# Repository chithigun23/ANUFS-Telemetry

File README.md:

# ANUFS Telemetry

Data-logging and telemetry module for the ANUFS vehicle: an STM32H523 board that listens on two CAN buses, fuses dual-antenna GNSS and an IMU with them, and logs everything to two microSD cards.

| Folder | What is in it | Start here |
|---|---|---|
| [hardware/](hardware/) | KiCad project, fabrication files, BOM, power budget, RF analysis | [hardware/README.md](hardware/README.md) |
| [software/](software/) | Rust firmware crates, host tools and diagrams | [software/README.md](software/README.md) |

## Where things stand

- **Hardware:** boards are ordered and will be assembled by hand. Fit R10 as 73.2k (the BOM is up to date). Fit J12 as the SWD header until the Tag-Connect cable arrives.
- **Software:** every logic crate and host tool is written and tested on the PC (332 tests), and the firmware (a bring-up self-test and the logger) builds for the chip. Nothing has run on the board yet; assembly is in [hardware/ASSEMBLY.md](hardware/ASSEMBLY.md) and the bring-up order is in [software/README.md](software/README.md).
- **Waiting on you:** the MoTeC CAN configuration (bit rate and message layouts), and a debug probe.

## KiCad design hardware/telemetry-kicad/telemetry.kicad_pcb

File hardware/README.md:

# ANUFS Telemetry

STM32H5-based data-logging and telemetry module for the ANUFS vehicle. It sits on two of the car's CAN buses, fuses IMU + dual-antenna GNSS data with bus traffic, logs everything to two microSD cards, drives onboard status LEDs, and exposes USB-C for bench debug.

Reference designators below come from the current netlist (`telemetry.net`, exported 2026-10-13).

## Architecture

- **Power** - the board runs from the vehicle's 12V harness input (`J1`), through `D2` (SMBJ16A TVS) and `F1` (1.5A polyfuse), then `Q1` (P-FET reverse-polarity protection, gate clamped by `D1`) into `U2` (TPS2121), which arbitrates between that battery feed and USB-C bus power (via `D3`) so the board can run on the bench without the car. The over-voltage lockout on the battery input is set by the `U2` OV1 divider (`R10` 73.2k / `R12` 5k). The muxed rail (`V_IN`) feeds two independent regulators: `U1` (LMR33610) bucks it to the **+3.3V rail that powers everything else on the board**, while `U5` (LM2940-5.0) makes a separate **+5V rail that goes only to the status LEDs' common anodes**.
- **Compute** - `U6`, an STM32H523RCT7 (Cortex-M33), is the hub. It is clocked from a 24MHz crystal (`Y1`). `SW3` is the NRST button and `SW4` pulls BOOT0 high (with `R34` pull-down) for the system bootloader.
- **Sensing** - `U3` (ASM330LHHX) is a 6-axis IMU wired to the MCU over SPI (CS, SCK, SDI, SDO), with INT1/INT2 back to the MCU (its MSDA/MSCL pins are tied to GND).
- **GNSS** - two Quectel LC29HEAMD modules form a dual-antenna moving-base heading pair:
  - `U10` is the **moving base**. It is the only module with a data link to the MCU: UART1 (TXD1/RXD1) and 1PPS go through `U12` (TXS0104E) because the module runs its digital I/O at 2.8V (`VDD_EXT_1`).
  - `U13` is the **rover**. Its only connection to the MCU is its 1PPS output (also through `U12`). It talks to `U10` on the `CORRECTION` (U10 pin 18 to U13 pin 21) and `HEADING` (U13 pin 20 to U10 pin 19) nets, and its reset (`GNSS_RESET_SLAVE`) is driven from U10 pin 17.
  - The MCU resets `U10` through `Q2` (MMBT3904, driven by `GNSS_RESET_ASSERT` via `R37`).
  - Each module has its own SMA (`J7` for U10, `J8` for U13) with a bias-tee for an active antenna (see [antenna doc](active_antenna_addition_BOM.md)). `J9`/`J10` are two further SMAs joined only to each other on net `ANT3` (RF test through-path, not connected to either module).
- **Comms** - two independent `TCAN337` transceivers (`U4`, `U7`) put the MCU on two CAN buses in parallel, broken out to `J4` (CAN1) and `J5` (CAN2).
- **Storage** - two microSD slots. `J3` (SD1) has CMD, CLK, D0-D3 and card-detect all routed to the MCU. `J11` (SD2) routes only CMD, CLK, D0, D3/CS and card-detect to the MCU; its DAT1 and DAT2 lines go to pull-ups only.
- **I/O & debug** - USB-C (`J6`, ESD-protected by `U11` USBLC6) is the bench data/debug link (D+/D- to the MCU). `J2` is a Tag-Connect TC2030 SWD port (SWDIO, SWCLK, NRST, SWO); `J12` is an alternative 1x04 SWD header on the same nets, not fitted (DNP) - only one of J2/J12 is ever installed. `SW1` and `SW2` are three-pin user switches (nets `SW_A`..`SW_D` to MCU pins PC0..PC3).
- **Status** - five bi-colour LEDs (`LED1`..`LED5`, XL-2012SURUGC) with common anodes on the +5V rail. Two `TLC59108` I2C drivers each sink one cathode channel per LED: `U9` drives nets `LED0`..`LED4` (LED pin 3 of each part) and `U8` drives `LED5`..`LED9` (LED pin 1 of each part), so the two colours are independently addressable per LED. `U8` has A0-A3 tied low and `U9` has A0 tied to +3.3V (A1-A3 low), giving them different I2C addresses. Both share SDA/SCL (4.7k pull-ups) and a common reset line driven by the MCU.

The diagram above is a live SVG: dashed lines are active power/signal paths and the small dots trace the direction of flow through each domain (open `assets/architecture.svg` directly if your viewer doesn't animate it).

## MCU pin map (U6, STM32H523RCT7, LQFP64)

Package pin numbers and nets as exported in `telemetry.net`. Alternate-function selection is not listed here; check it against the ST datasheet when configuring peripherals.

| Function | Signal (net) | MCU pin (package pin) |
|---|---|---|
| Crystal | CYST_IN / CYST_OUT | PH0 (5) / PH1 (6) |
| Reset | NRST | NRST (7) |
| Boot | BOOT0 | BOOT0 (60) |
| SWD | SWDIO / SWCLK / SWO | PA13 (46) / PA14 (49) / PB3 (55) |
| USB | D- / D+ | PA11 (44) / PA12 (45) |
| User switches | SW_A / SW_B / SW_C / SW_D | PC0 (8) / PC1 (9) / PC2 (10) / PC3 (11) |
| GNSS U10 UART | RXD1_GNSS / TXD1_GNSS (MCU-side names) | PA0 (14) / PA1 (15) |
| GNSS 1PPS | TIMERIN_GNSS_1 (U10) / TIMERIN_GNSS_2 (U13) | PA9 (42) / PA3 (17) |
| GNSS reset | GNSS_RESET_ASSERT (to Q2 base) | PC6 (37) |
| IMU | CS_IMU / SCK_IMU / DO_IMU / DI_IMU | PA4 (20) / PA5 (21) / PA6 (22) / PA7 (23) |
| IMU interrupts | INT1 / INT2 | PC4 (24) / PC5 (25) |
| CAN1 | TXD_CAN1 / RXD_CAN1 / FLT_CAN1 | PB7 (59) / PB8 (61) / PB6 (58) |
| CAN2 | TXD_CAN2 / RXD_CAN2 / FLT_CAN2 / SIL_CAN2 | PB13 (34) / PB12 (33) / PB10 (29) / PA10 (43) |
| SD1 (J3) | D0 / D1 / D2 / D3 | PC8 (39) / PC9 (40) / PC10 (51) / PC11 (52) |
| SD1 (J3) | CLK / CMD / DET | PC12 (53) / PD2 (54) / PC7 (38) |
| SD2 (J11) | D0 / D3 (CS) / CLK / CMD / DET | PB14 (35) / PB0 (26) / PB2 (28) / PB15 (36) / PB1 (27) |
| LED drivers | SCL_LED / SDA_LED / RST_LED | PA8 (41) / PB4 (56) / PB5 (57) |
| Unconnected | PC13, PC14, PC15, PA2, PA15 | 2, 3, 4, 16, 50 |

## Repo contents

- [KiCad project](telemetry-kicad/telemetry.kicad_pro)
- [Schematic](telemetry-kicad/telemetry.kicad_sch)
- [PCB layout](telemetry-kicad/telemetry.kicad_pcb)
- [Netlist](telemetry.net)
- [JLCPCB gerbers](telemetry-kicad/JLCPCB_gerbers) and [fab zip](telemetry-kicad/telemetry-JLCPCB.zip)
- [Bill of materials](TELEMETRY_DigiKey_BOM.xlsx)
- [Power budget](telemetry_power_budget.xlsx) (stale: it predates the second GNSS module and SD2)
- [Active antenna and dual-antenna heading notes](active_antenna_addition_BOM.md)
- [RF analysis](RF%20Analysis/STATUS.md)
- [Firmware / software](../software)

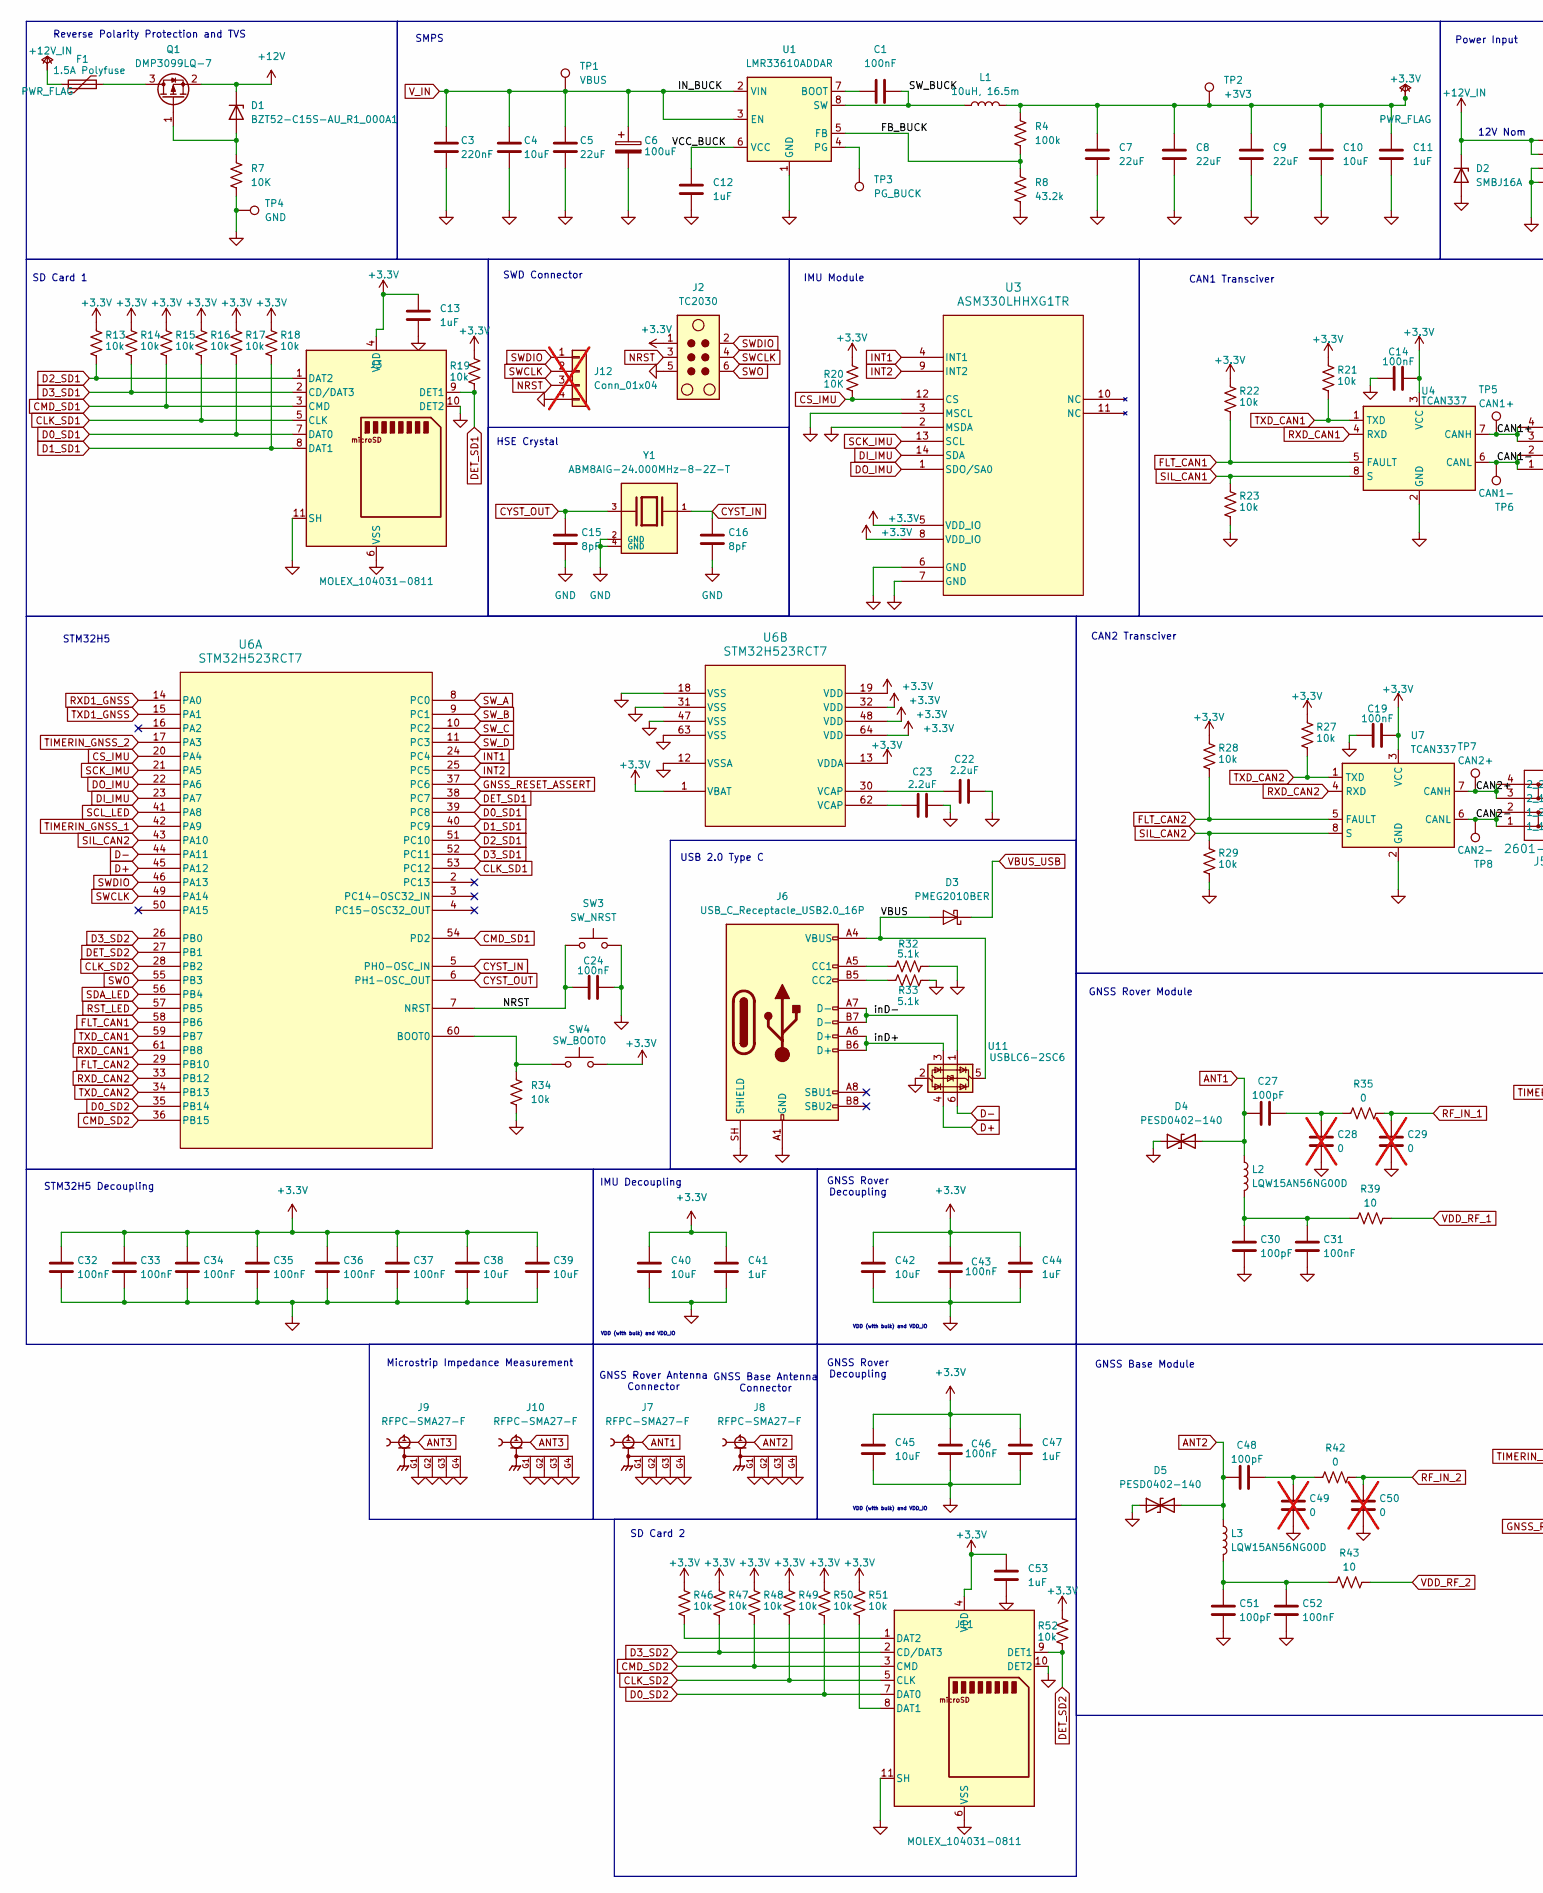
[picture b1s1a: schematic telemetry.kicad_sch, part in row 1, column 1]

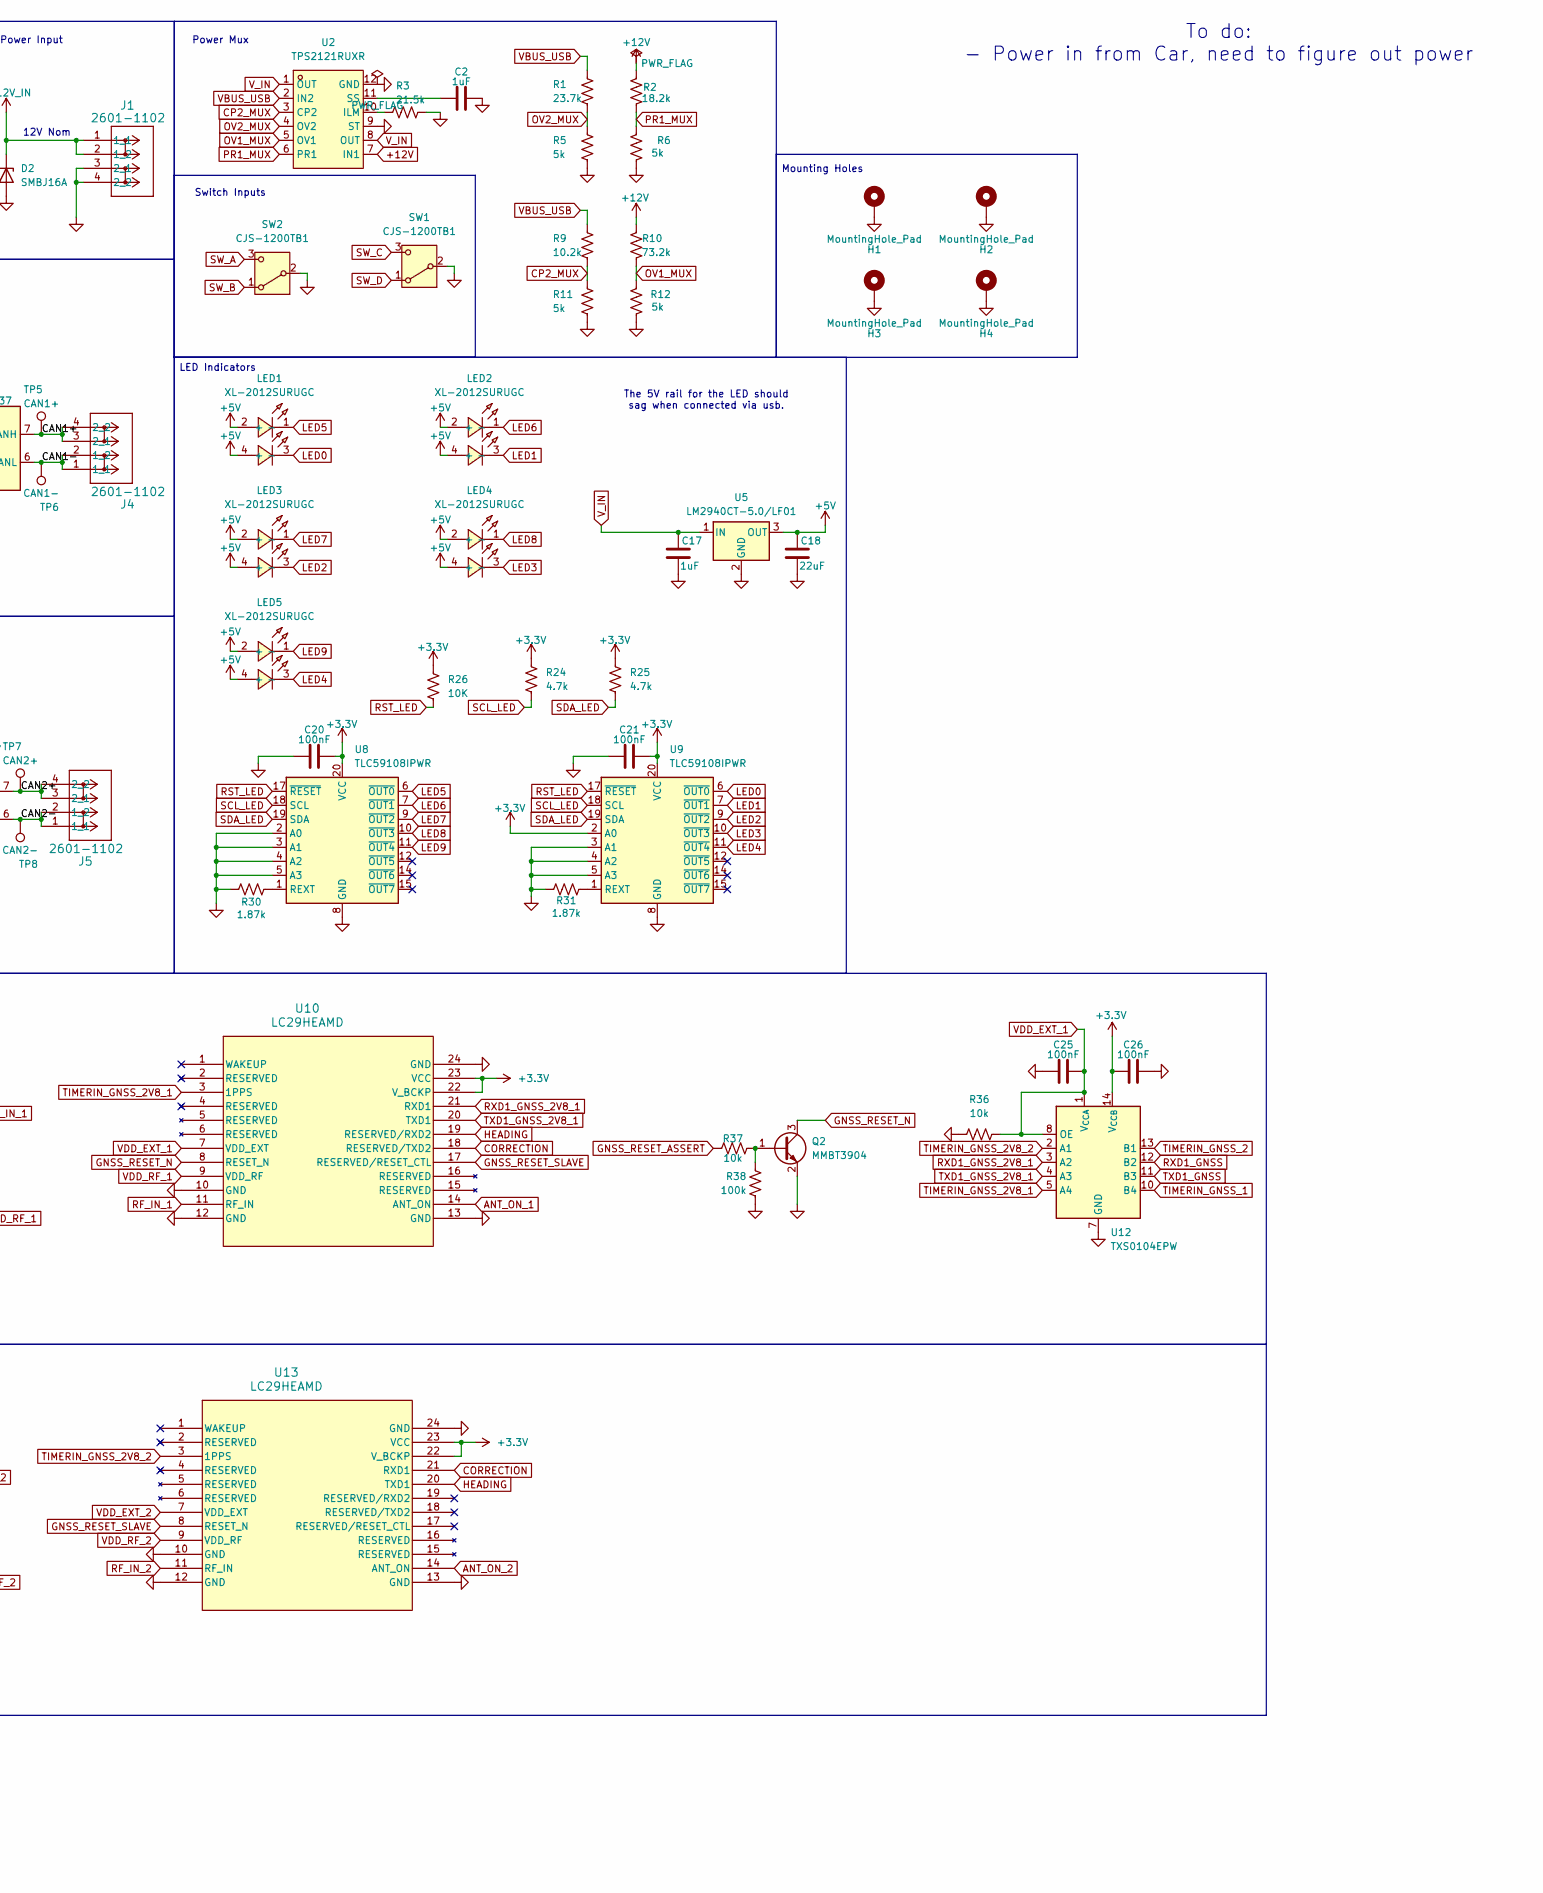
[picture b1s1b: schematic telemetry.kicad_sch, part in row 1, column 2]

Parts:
C1, C14, C19, C20, C21, C24, C25, C26, C31, C32, C33, C34, C35, C36, C37, C43, C46, C52: 100nF; C_0402_1005Metric_Pad0.74x0.62mm_HandSolder
C2, C11, C12, C13, C17, C41, C44, C47, C53: 1uF; C_0402_1005Metric_Pad0.74x0.62mm_HandSolder
C3: 220nF; C_0402_1005Metric_Pad0.74x0.62mm_HandSolder
C4, C10, C38, C39, C40, C42, C45: 10uF; C_0402_1005Metric_Pad0.74x0.62mm_HandSolder
C5, C7, C8, C9, C18: 22uF; C_0402_1005Metric_Pad0.74x0.62mm_HandSolder
C6: 100uF; CP_Elec_6.3x7.7
C15, C16: 8pF; C_0402_1005Metric_Pad0.74x0.62mm_HandSolder
C22, C23: 2.2uF; C_0402_1005Metric_Pad0.74x0.62mm_HandSolder
C27, C30, C48, C51: 100pF; C_0402_1005Metric_Pad0.74x0.62mm_HandSolder
C28, C29, C49, C50: 0; C_0402_1005Metric_Pad0.74x0.62mm_HandSolder; not fitted
D1: BZT52-C15S-AU_R1_000A1; D_SOD-123
D2: SMBJ16A; MPN SMBJ16A; LCSC Part C151254
D3: PMEG2010BER; Nexperia_CFP3_SOD-123W
D4, D5: PESD0402-140; MPN PESD0402-140; LCSC Part C10662
F1: 1.5A Polyfuse; L_1812_4532Metric_Pad1.30x3.40mm_HandSolder
H1, H2, H3, H4: MountingHole_Pad; MountingHole_3.2mm_M3_Pad
J1, J4, J5: 2601-1102; WAGO-2601-1102
J2: TC2030; Tag-Connect_TC2030-IDC-FP_2x03_P1.27mm_Vertical
J3, J11: MOLEX_104031-0811
J6: USB_C_Receptacle_USB2.0_16P; USB-C-SMD_TYPE-C-16PIN-2MD-073
J7, J8, J9, J10: RFPC-SMA27-F; PARTREV 1.0
J12: Conn_01x04; PinHeader_1x04_P2.54mm_Vertical; not fitted
L1: 10uH, 16.5m; L_TaiTech_TMPC1265_13.5x12.5mm
L2, L3: LQW15AN56NG00D; MPN LQW15AN56NG00D; LCSC Part C167482
LED1, LED2, LED3, LED4, LED5: XL-2012SURUGC; MPN XL-2012SURUGC; LCSC Part C965845
Q1: DMP3099LQ-7; SOT-23
Q2: MMBT3904; SOT-23
R1: 23.7k; R_0402_1005Metric_Pad0.72x0.64mm_HandSolder
R2: 18.2k; R_0402_1005Metric_Pad0.72x0.64mm_HandSolder
R3: 21.5k; R_0402_1005Metric_Pad0.72x0.64mm_HandSolder
R4, R38: 100k; R_0402_1005Metric_Pad0.72x0.64mm_HandSolder
R5, R6, R11, R12: 5k; R_0402_1005Metric_Pad0.72x0.64mm_HandSolder
R7, R20, R26: 10K; R_0402_1005Metric_Pad0.72x0.64mm_HandSolder
R8: 43.2k; R_0402_1005Metric_Pad0.72x0.64mm_HandSolder
R9: 10.2k; R_0402_1005Metric_Pad0.72x0.64mm_HandSolder
R10: 73.2k; R_0402_1005Metric_Pad0.72x0.64mm_HandSolder
R13, R14, R15, R16, R17, R18, R19, R21, R22, R23, R27, R28, R29, R34, R36, R37, R46, R47, R48, R49, R50, R51, R52: 10k; R_0402_1005Metric_Pad0.72x0.64mm_HandSolder
R24, R25: 4.7k; R_0402_1005Metric_Pad0.72x0.64mm_HandSolder
R30, R31: 1.87k; R_0402_1005Metric_Pad0.72x0.64mm_HandSolder
R32, R33: 5.1k; R_0402_1005Metric_Pad0.72x0.64mm_HandSolder
R35, R42: 0; R_0402_1005Metric_Pad0.72x0.64mm_HandSolder
R39, R43: 10; R_0402_1005Metric_Pad0.72x0.64mm_HandSolder
SW1, SW2: CJS-1200TB1; MPN CJS-1200TB1; LCSC Part C2921631
SW3: SW_NRST; SMD-Switch
SW4: SW_BOOT0; SMD-Switch
TP1: VBUS; TestPoint_THTPad_D2.0mm_Drill1.0mm
TP2: +3V3; TestPoint_THTPad_D2.0mm_Drill1.0mm
TP3: PG_BUCK; TestPoint_THTPad_D2.0mm_Drill1.0mm
TP4: GND; TestPoint_THTPad_D2.0mm_Drill1.0mm
TP5: CAN1+; TestPoint_THTPad_D2.0mm_Drill1.0mm
TP6: CAN1-; TestPoint_THTPad_D2.0mm_Drill1.0mm
TP7: CAN2+; TestPoint_THTPad_D2.0mm_Drill1.0mm
TP8: CAN2-; TestPoint_THTPad_D2.0mm_Drill1.0mm
U1: LMR33610ADDAR; Texas_HSOP-8-1EP_3.9x4.9mm_P1.27mm_ThermalVias
U2: TPS2121RUXR; VQFN-HR-12_L2.5-W2.0-P0.50-BL; MPN TPS2121RUXR; LCSC Part C485916
U3: ASM330LHHXG1TR
U4, U7: TCAN337; SOIC-8_3.9x4.9mm_P1.27mm
U5: LM2940CT-5.0/LF01; TO-263-3_TabPin2; MPN LM2940CT-5.0/LF01
U6: STM32H523RCT7
U8, U9: TLC59108IPWR; MPN TLC59108IPWR
U10, U13: LC29HEAMD
U11: USBLC6-2SC6; SOT-23-6
U12: TXS0104EPW; TSSOP-14_4.4x5mm_P0.65mm
Y1: ABM8AIG-24.000MHz-8-2Z-T; ABM8AIG-24.000MHZ-8-2Z-T; PARTREV 43629

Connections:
+3.3V: C7.1, C8.1, C9.1, C10.2, C11.1, C13.1, C14.2, C19.2, C20.2, C21.2, C26.1, C32.1, C33.1, C34.1, C35.1, C36.1, C37.1, C38.1, C39.1, C40.2, C41.1, C42.2, C43.2, C44.1, C45.2, C46.2, C47.1, C53.1, J2.1, J3.4 (VDD), J11.4 (VDD), L1.2, R4.1, R13.1, R14.1, R15.1, R16.1, R17.1, R18.1, R19.1, R20.1, R21.1, R22.1, R24.1, R25.1, R26.1, R27.1, R28.1, R46.1, R47.1, R48.1, R49.1, R50.1, R51.1, R52.1, SW4.2, TP2.1 (1_1), U3.5 (VDD_IO), U3.8 (VDD_IO), U4.3 (VCC), U6.1 (VBAT), U6.13 (VDDA), U6.19 (VDD), U6.32 (VDD), U6.48 (VDD), U6.64 (VDD), U7.3 (VCC), U8.20 (VCC), U9.2 (A0), U9.20 (VCC), U10.22 (V_BCKP), U10.23 (VCC), U12.14 (V_{CCB}), U13.22 (V_BCKP), U13.23 (VCC)
+5V: C18.2, LED1.2 (+), LED1.4 (+), LED2.2 (+), LED2.4 (+), LED3.2 (+), LED3.4 (+), LED4.2 (+), LED4.4 (+), LED5.2 (+), LED5.4 (+), U5.3 (OUT)
+12V: D1.1 (K), Q1.2 (S), R2.1, R10.1, U2.7 (IN1)
+12V_IN: D2.1 (K), F1.1, J1.1 (1_1), J1.2 (1_2)
/CAN1+: J4.3 (2_1), J4.4 (2_2), TP5.1 (1_1), U4.7 (CANH)
/CAN1-: J4.1 (1_1), J4.2 (1_2), TP6.1 (1_1), U4.6 (CANL)
/CAN2+: J5.3 (2_1), J5.4 (2_2), TP7.1 (1_1), U7.7 (CANH)
/CAN2-: J5.1 (1_1), J5.2 (1_2), TP8.1 (1_1), U7.6 (CANL)
/FB_BUCK: R4.2, R8.1, U1.5 (FB)
/SW_BUCK: C1.2, L1.1, U1.8 (SW)
/VBUS: D3.2 (A), J6.A4 (VBUS), U11.5 (VBUS)
/VCC_BUCK: C12.1, U1.6 (VCC)
/inD+: J6.A6 (D+), J6.B6 (D+), U11.3 (I/O2)
/inD-: J6.A7 (D-), J6.B7 (D-), U11.1 (I/O1)
ANT1: C27.1, D4.2 (A2), J7.1, L2.1
ANT2: C48.1, D5.2 (A2), J8.1, L3.1
ANT3: J9.1, J10.1
ANT_ON_1: U10.14 (ANT_ON)
ANT_ON_2: U13.14 (ANT_ON)
CLK_SD1: J3.5 (CLK), R16.2, U6.53 (PC12)
CLK_SD2: J11.5 (CLK), R49.2, U6.28 (PB2)
CMD_SD1: J3.3 (CMD), R15.2, U6.54 (PD2)
CMD_SD2: J11.3 (CMD), R48.2, U6.36 (PB15)
CORRECTION: U10.18 (RESERVED/TXD2), U13.21 (RXD1)
CP2_MUX: R9.2, R11.1, U2.3 (CP2)
CS_IMU: R20.2, U3.12 (CS), U6.20 (PA4)
CYST_IN: C16.1, U6.5 (PH0-OSC_IN), Y1.1
CYST_OUT: C15.1, U6.6 (PH1-OSC_OUT), Y1.3
D0_SD1: J3.7 (DAT0), R17.2, U6.39 (PC8)
D0_SD2: J11.7 (DAT0), R50.2, U6.35 (PB14)
D1_SD1: J3.8 (DAT1), R18.2, U6.40 (PC9)
D2_SD1: J3.1 (DAT2), R13.2, U6.51 (PC10)
D3_SD1: J3.2 (CD/DAT3), R14.2, U6.52 (PC11)
D3_SD2: J11.2 (CD/DAT3), R47.2, U6.26 (PB0)
D+: U6.45 (PA12), U11.4 (I/O2)
D-: U6.44 (PA11), U11.6 (I/O1)
DET_SD1: J3.9 (DET1), R19.2, U6.38 (PC7)
DET_SD2: J11.9 (DET1), R52.2, U6.27 (PB1)
DI_IMU: U3.14 (SDA), U6.23 (PA7)
DO_IMU: U3.1 (SDO/SA0), U6.22 (PA6)
FLT_CAN1: R22.2, U4.5 (FAULT), U6.58 (PB6)
FLT_CAN2: R28.2, U6.29 (PB10), U7.5 (FAULT)
GND: C2.2, C3.2, C4.2, C5.2, C6.2, C7.2, C8.2, C9.2, C10.1, C11.2, C12.2, C13.2, C14.1, C15.2, C16.2, C17.1, C18.1, C19.1, C20.1, C21.1, C22.2, C23.2, C24.2, C25.1, C26.2, C28.2, C29.2, C30.2, C31.2, C32.2, C33.2, C34.2, C35.2, C36.2, C37.2, C38.2, C39.2, C40.1, C41.2, C42.1, C43.1, C44.2, C45.1, C46.1, C47.2, C49.2, C50.2, C51.2, C52.2, C53.2, D2.2 (A), D4.1 (A1), D5.1 (A1), H1.1 (1_1), H2.1 (1_1), H3.1 (1_1), H4.1 (1_1), J1.3 (2_1), J1.4 (2_2), J2.5, J3.6 (VSS), J3.10 (DET2), J3.11 (SH), J6.A1 (GND), J6.SH (SHIELD), J7.G1, J7.G2, J7.G3, J7.G4, J8.G1, J8.G2, J8.G3, J8.G4, J9.G1, J9.G2, J9.G3, J9.G4, J10.G1, J10.G2, J10.G3, J10.G4, J11.6 (VSS), J11.10 (DET2), J11.11 (SH), J12.4, Q2.2 (E), R3.2, R5.2, R6.2, R7.2, R8.2, R11.2, R12.2, R23.2, R29.2, R30.1, R31.1, R32.2, R33.2, R34.2, R36.1, R38.2, SW1.2 (B), SW2.2 (B), SW3.2, TP4.1 (1_1), U1.1 (GND), U1.9 (GND), U2.9 (ST), U2.12 (GND), U3.2 (MSDA), U3.3 (MSCL), U3.6 (GND), U3.7 (GND), U4.2 (GND), U5.2 (GND), U6.12 (VSSA), U6.18 (VSS), U6.31 (VSS), U6.47 (VSS), U6.63 (VSS), U7.2 (GND), U8.2 (A0), U8.3 (A1), U8.4 (A2), U8.5 (A3), U8.8 (GND), U8.13 (GND), U8.16 (GND), U9.3 (A1), U9.4 (A2), U9.5 (A3), U9.8 (GND), U9.13 (GND), U9.16 (GND), U10.10 (GND), U10.12 (GND), U10.13 (GND), U10.24 (GND), U11.2 (GND), U12.7 (GND), U13.10 (GND), U13.12 (GND), U13.13 (GND), U13.24 (GND), Y1.2 (GND), Y1.4 (GND)
GNSS_RESET_ASSERT: R37.1, U6.37 (PC6)
GNSS_RESET_N: Q2.3 (C), U10.8 (RESET_N)
GNSS_RESET_SLAVE: U10.17 (RESERVED/RESET_CTL), U13.8 (RESET_N)
HEADING: U10.19 (RESERVED/RXD2), U13.20 (TXD1)
INT1: U3.4 (INT1), U6.24 (PC4)
INT2: U3.9 (INT2), U6.25 (PC5)
LED0: LED1.3 (-), U9.6 (~OUT0)
LED1: LED2.3 (-), U9.7 (~OUT1)
LED2: LED3.3 (-), U9.9 (~OUT2)
LED3: LED4.3 (-), U9.10 (~OUT3)
LED4: LED5.3 (-), U9.11 (~OUT4)
LED5: LED1.1 (-), U8.6 (~OUT0)
LED6: LED2.1 (-), U8.7 (~OUT1)
LED7: LED3.1 (-), U8.9 (~OUT2)
LED8: LED4.1 (-), U8.10 (~OUT3)
LED9: LED5.1 (-), U8.11 (~OUT4)
NRST: C24.1, J2.3, J12.3, SW3.1, U6.7 (NRST)
unnamed: C22.1, U6.30 (VCAP)
unnamed: C23.1, U6.62 (VCAP)
unnamed: C27.2, C28.1, R35.1
unnamed: C30.1, C31.1, L2.2, R39.1
unnamed: C48.2, C49.1, R42.1
unnamed: C51.1, C52.1, L3.2, R43.1
unnamed: D1.2 (A), Q1.1 (G), R7.1
unnamed: J6.A5 (CC1), R32.1
unnamed: J6.B5 (CC2), R33.1
unnamed: J11.8 (DAT1), R51.2
unnamed: J11.1 (DAT2), R46.2
unnamed: F1.2, Q1.3 (D)
unnamed: Q2.1 (B), R37.2, R38.1
unnamed: C1.1, U1.7 (BOOT)
unnamed: TP3.1 (1_1), U1.4 (PG)
unnamed: R3.1, U2.10 (ILM)
unnamed: C2.1, U2.11 (SS)
unnamed: R34.1, SW4.1, U6.60 (BOOT0)
unnamed: R30.2, U8.1 (REXT)
unnamed: R31.2, U9.1 (REXT)
OV1_MUX: R10.2, R12.1, U2.5 (OV1)
OV2_MUX: R1.2, R5.1, U2.4 (OV2)
PR1_MUX: R2.2, R6.1, U2.6 (PR1)
RF_IN_1: C29.1, R35.2, U10.11 (RF_IN)
RF_IN_2: C50.1, R42.2, U13.11 (RF_IN)
RST_LED: R26.2, U6.57 (PB5), U8.17 (~RESET), U9.17 (~RESET)
RXD1_GNSS: U6.14 (PA0), U12.12 (B2)
RXD1_GNSS_2V8_1: U10.21 (RXD1), U12.3 (A2)
RXD_CAN1: U4.4 (RXD), U6.61 (PB8)
RXD_CAN2: U6.33 (PB12), U7.4 (RXD)
SCK_IMU: U3.13 (SCL), U6.21 (PA5)
SCL_LED: R24.2, U6.41 (PA8), U8.18 (SCL), U9.18 (SCL)
SDA_LED: R25.2, U6.56 (PB4), U8.19 (SDA), U9.19 (SDA)
SIL_CAN1: R23.1, U4.8 (S)
SIL_CAN2: R29.1, U6.43 (PA10), U7.8 (S)
SWCLK: J2.4, J12.2, U6.49 (PA14)
SWDIO: J2.2, J12.1, U6.46 (PA13)
SWO: J2.6, U6.55 (PB3)
SW_A: SW2.3 (C), U6.8 (PC0)
SW_B: SW2.1 (A), U6.9 (PC1)
SW_C: SW1.3 (C), U6.10 (PC2)
SW_D: SW1.1 (A), U6.11 (PC3)
TIMERIN_GNSS_1: U6.42 (PA9), U12.10 (B4)
TIMERIN_GNSS_2: U6.17 (PA3), U12.13 (B1)
TIMERIN_GNSS_2V8_1: U10.3 (1PPS), U12.5 (A4)
TIMERIN_GNSS_2V8_2: U12.2 (A1), U13.3 (1PPS)
TXD1_GNSS: U6.15 (PA1), U12.11 (B3)
TXD1_GNSS_2V8_1: U10.20 (TXD1), U12.4 (A3)
TXD_CAN1: R21.2, U4.1 (TXD), U6.59 (PB7)
TXD_CAN2: R27.2, U6.34 (PB13), U7.1 (TXD)
VBUS_USB: D3.1 (K), R1.1, R9.1, U2.2 (IN2)
VDD_EXT_1: C25.2, R36.2, U10.7 (VDD_EXT), U12.1 (V_{CCA}), U12.8 (OE)
VDD_EXT_2: U13.7 (VDD_EXT)
VDD_RF_1: R39.2, U10.9 (VDD_RF)
VDD_RF_2: R43.2, U13.9 (VDD_RF)
V_IN: C3.1, C4.1, C5.1, C6.1, C17.2, TP1.1 (1_1), U1.2 (VIN), U1.3 (EN), U2.1 (OUT), U2.8 (OUT), U5.1 (IN)

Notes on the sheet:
SMPS
GNSS Base Antenna Connector
SD Card 1
CAN1 Transciver
GNSS Base Module
STM32H5 Decoupling
GNSS Rover Module
STM32H5
The 5V rail for the LED should sag when connected via usb.
VDD (with bulk) and VDD_IO
SWD Connector
IMU Decoupling
Microstrip Impedance Measurement
GNSS Rover Antenna Connector
Reverse Polarity Protection and TVS
USB 2.0 Type C
GNSS Rover Decoupling
SD Card 2
Power Input
CAN2 Transciver
Mounting Holes
HSE Crystal
IMU Module
12V Nom
To do: - Power in from Car, need to figure out power
Switch Inputs
Power Mux
LED Indicators

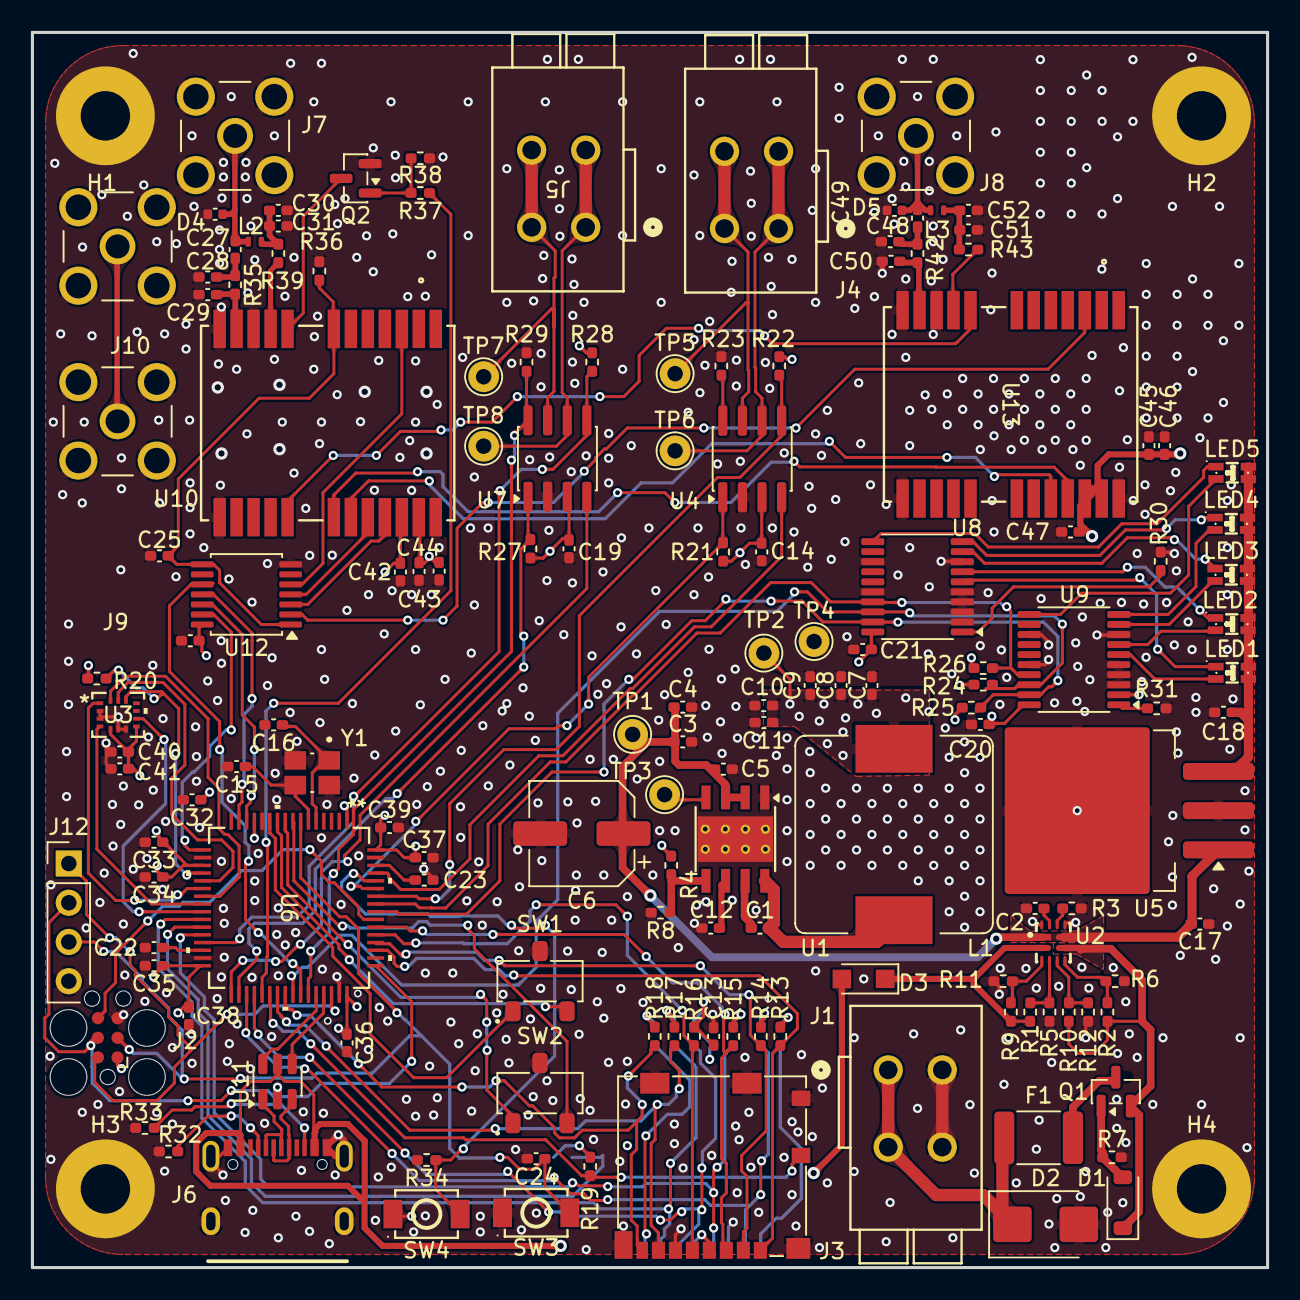
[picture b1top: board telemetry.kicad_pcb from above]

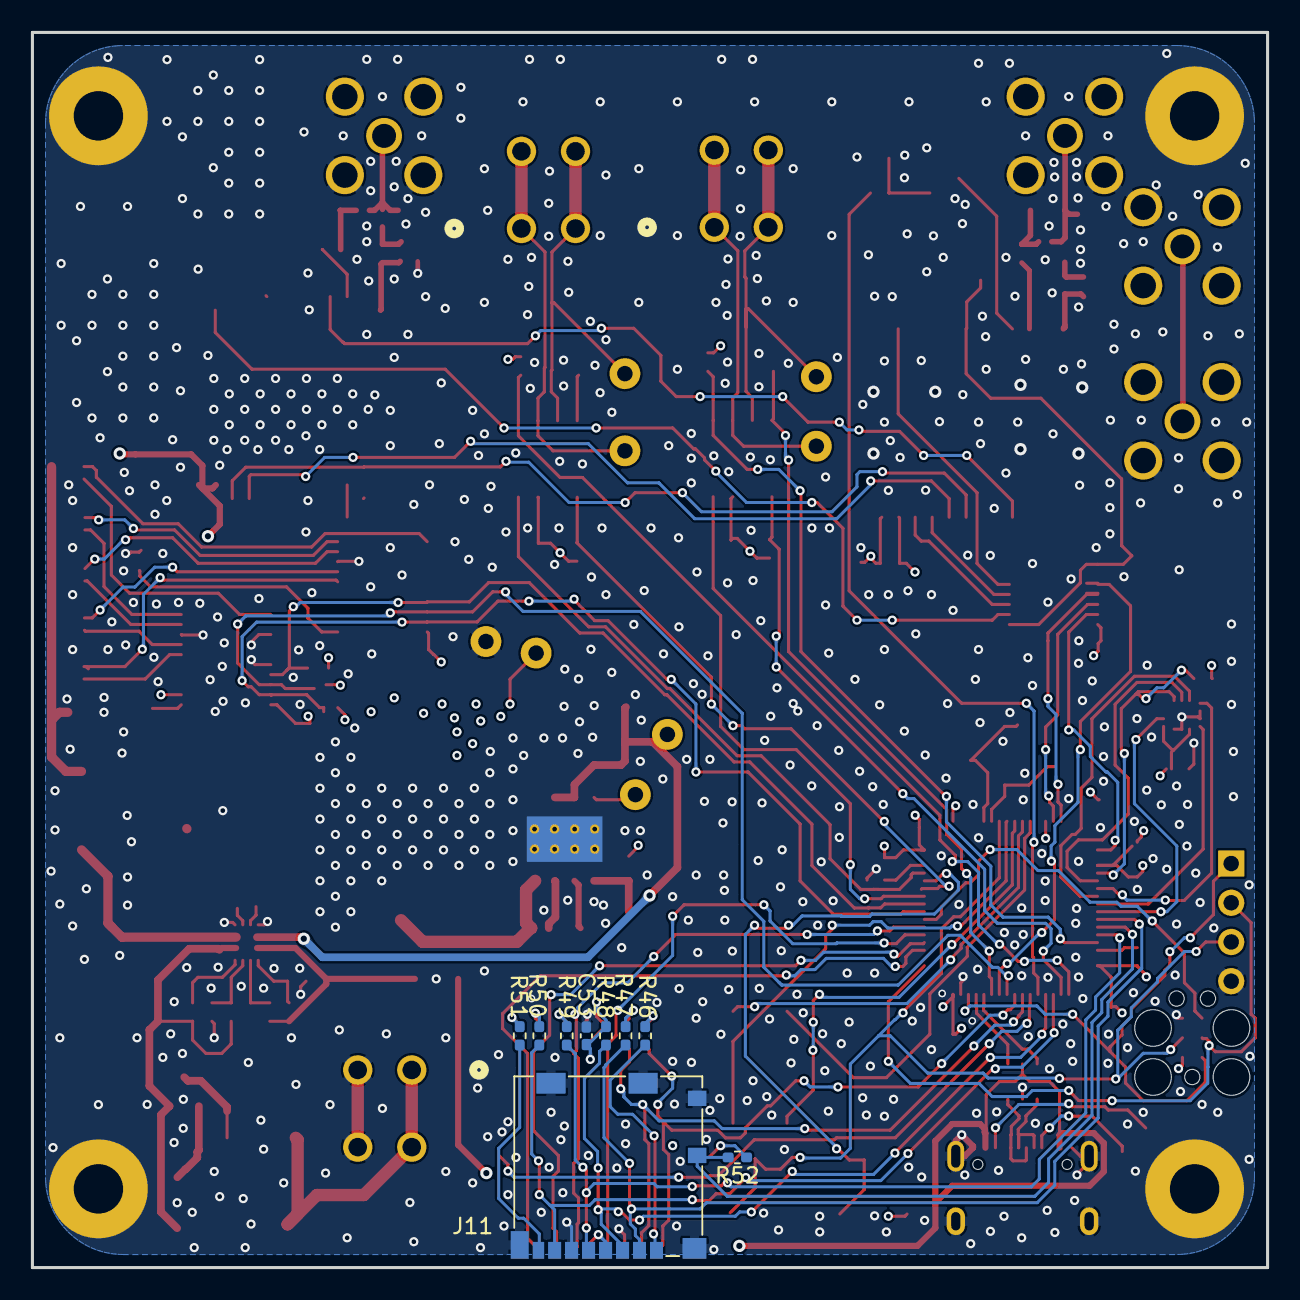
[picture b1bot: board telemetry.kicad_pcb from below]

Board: 4 copper layers, 80.0 x 80.0 mm, 159 parts (9 on the bottom side), 113 nets.

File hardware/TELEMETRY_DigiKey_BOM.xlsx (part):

# | Reference(s) | Qty | Value | Package / Footprint | Manufacturer | Manufacturer Part Number (MPN) | DigiKey Part Number | Purchasing spec / action | Notes
1 | C1,C14,C19-C21,C24-C26,C32-C37,C43,C46 | 16 | 100nF | C_0402_1005Metric_Pad0.74x0.62mm_HandSolder |  |  |  | Select exact supplier part matching value and footprint.
2 | C2,C11-C13,C17,C41,C44,C47,C53 | 9 | 1uF | C_0402_1005Metric_Pad0.74x0.62mm_HandSolder |  |  |  | Select exact supplier part matching value and footprint.
3 | C3 | 1 | 220nF | C_0402_1005Metric_Pad0.74x0.62mm_HandSolder |  |  |  | Select exact supplier part matching value and footprint.
4 | C4,C10,C38-C40,C42,C45 | 7 | 10uF | C_0402_1005Metric_Pad0.74x0.62mm_HandSolder |  |  |  | Select exact supplier part matching value and footprint.
5 | C5,C7-C9,C18 | 5 | 22uF | C_0402_1005Metric_Pad0.74x0.62mm_HandSolder |  |  |  | Select exact supplier part matching value and footprint.
6 | C6 | 1 | 100uF | CP_Elec_6.3x7.7 |  |  |  | Select exact supplier part matching value and footprint.
7 | C15,C16 | 2 | 8pF | C_0402_1005Metric_Pad0.74x0.62mm_HandSolder |  |  |  | Select exact supplier part matching value and footprint.
8 | C22,C23 | 2 | 2.2uF | C_0402_1005Metric_Pad0.74x0.62mm_HandSolder |  |  |  | Select exact supplier part matching value and footprint.
9 | C27,C30,C48,C51 | 4 | 100pF | C_0402_1005Metric_Pad0.74x0.62mm_HandSolder | Yageo | CC0402JRNPO9BN101 |  | Match package and ordering suffix. | LCSC: C106200. C0G/NP0, 50V, 5%. GNSS antenna bias-tee DC block or bias decoupl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
10 | C31,C52 | 2 | 100nF | C_0402_1005Metric_Pad0.74x0.62mm_HandSolder | Yageo | CC0402KRX7R7BB104 |  | Match package and ordering suffix. | LCSC: C60474. X7R, 16V, 10%. GNSS antenna bias-tee decoupling cap (source: acti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
11 | D1 | 1 | BZT52-C15S-AU_R1_000A1 | D_SOD-123 |  | BZT52-C15S-AU_R1_000A1 |  | Match package and ordering suffix. | Part identifier from schematic value; verify exact ordering code.
12 | D2 | 1 | SMBJ16A | SMBJ16A | Littelfuse | SMBJ16A |  | Match package and ordering suffix. | LCSC: C151254
13 | D3 | 1 | PMEG2010BER | Nexperia_CFP3_SOD-123W |  | PMEG2010BER |  | Match package and ordering suffix. | Part identifier from schematic value; verify exact ordering code.
14 | D4,D5 | 2 | PESD0402-140 | PESD0402-140 | Littelfuse | PESD0402-140 | PESD0402-140CT-ND | Match package and ordering suffix. | LCSC: C10662. ESD protection at the GNSS antenna node.
15 | F1 | 1 | 1.5A Polyfuse | L_1812_4532Metric_Pad1.30x3.40mm_HandSolder |  |  |  | Select exact supplier part matching value and footprint.
16 | J1,J4,J5 | 3 | 2601-1102 | WAGO-2601-1102 |  |  |  | Select exact supplier part matching value and footprint.
17 | J3,J11 | 2 | MOLEX_104031-0811 | MOLEX_104031-0811 |  |  |  | Select exact supplier part matching value and footprint.
18 | J6 | 1 | USB_C_Receptacle_USB2.0_16P | USB-C-SMD_TYPE-C-16PIN-2MD-073 |  |  |  | Select exact supplier part matching value and footprint. | LCSC: C2765186
19 | J7-J10 | 4 | RFPC-SMA27-F | RFPC-SMA27-F | GradConn | RFPC-SMA27-F |  | Match package and ordering suffix. | J7 and J8 are the GNSS antenna inputs. J9 and J10 are joined to each other on n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
20 | L1 | 1 | 8uH, 14m | L_TaiTech_TMPC1265_13.5x12.5mm |  |  |  | Select exact supplier part matching value and footprint.
21 | L2,L3 | 2 | LQW15AN56NG00D | LQW15AN56NG00D | Murata | LQW15AN56NG00D | 490-6830-1-ND | Match package and ordering suffix. | LCSC: C167482. 56nH GNSS antenna bias choke, SRF 2.8GHz (source: active_antenna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
22 | LED1-LED5 | 5 | XL-2012SURUGC | XL-2012SURUGC | XINGLIGHT(成兴光) | XL-2012SURUGC |  | Match package and ordering suffix. | LCSC: C965845
23 | Q1 | 1 | DMP3099LQ-7 | SOT-23 |  | DMP3099LQ-7 |  | Match package and ordering suffix. | Part identifier from schematic value; verify exact ordering code.
24 | Q2 | 1 | MMBT3904 | SOT-23 |  | MMBT3904 |  | Match package and ordering suffix. | Part identifier from schematic value; verify exact ordering code.
25 | R1 | 1 | 23.7k | R_0402_1005Metric_Pad0.72x0.64mm_HandSolder |  |  |  | Select exact supplier part matching value and footprint.
26 | R2 | 1 | 18.2k | R_0402_1005Metric_Pad0.72x0.64mm_HandSolder |  |  |  | Select exact supplier part matching value and footprint.
27 | R3 | 1 | 21.5k | R_0402_1005Metric_Pad0.72x0.64mm_HandSolder |  |  |  | Select exact supplier part matching value and footprint.
28 | R4,R38 | 2 | 100k | R_0402_1005Metric_Pad0.72x0.64mm_HandSolder |  |  |  | Select exact supplier part matching value and footprint.
29 | R5,R6,R11,R12 | 4 | 5k | R_0402_1005Metric_Pad0.72x0.64mm_HandSolder |  |  |  | Select exact supplier part matching value and footprint.
30 | R7,R13-R23,R26-R29,R34,R36,R37,R46-R52 | 26 | 10k | R_0402_1005Metric_Pad0.72x0.64mm_HandSolder |  |  |  | Select exact supplier part matching value and footprint.
31 | R8 | 1 | 43.2k | R_0402_1005Metric_Pad0.72x0.64mm_HandSolder |  |  |  | Select exact supplier part matching value and footprint.
32 | R9 | 1 | 10.2k | R_0402_1005Metric_Pad0.72x0.64mm_HandSolder |  |  |  | Select exact supplier part matching value and footprint.
33 | R10 | 1 | 73.2k | R_0402_1005Metric_Pad0.72x0.64mm_HandSolder |  |  |  | Select exact supplier part matching value and footprint. | 73.2k sets the TPS2121 OV1 trip. Trip = VREF x (1 + R10/R12) with VREF 1.01/1.0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
34 | R24,R25 | 2 | 4.7k | R_0402_1005Metric_Pad0.72x0.64mm_HandSolder |  |  |  | Select exact supplier part matching value and footprint.
35 | R30,R31 | 2 | 1.87k | R_0402_1005Metric_Pad0.72x0.64mm_HandSolder |  |  |  | Select exact supplier part matching value and footprint.
36 | R32,R33 | 2 | 5.1k | R_0402_1005Metric_Pad0.72x0.64mm_HandSolder |  |  |  | Select exact supplier part matching value and footprint.
37 | R35,R42 | 2 | 0 | R_0402_1005Metric_Pad0.72x0.64mm_HandSolder |  |  |  | Select exact supplier part matching value and footprint. | 0 ohm link in the RF pi-filter series position, populated.
38 | R39,R43 | 2 | 10 | R_0402_1005Metric_Pad0.72x0.64mm_HandSolder |  |  |  | Select exact supplier part matching value and footprint. | GNSS antenna bias series resistor, limits fault current if the antenna connecto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
39 | SW1,SW2 | 2 | CJS-1200TB1 | CJS-1200TB1 | Nidec Components | CJS-1200TB1 |  | Match package and ordering suffix. | LCSC: C2921631
40 | SW3 | 1 | SW_NRST | SMD-Switch |  |  |  | Select exact supplier part matching value and footprint.
41 | SW4 | 1 | SW_BOOT0 | SMD-Switch |  |  |  | Select exact supplier part matching value and footprint.
42 | TP1 | 1 | VBUS | TestPoint_THTPad_D2.0mm_Drill1.0mm |  |  |  | Optional physical test point; select matching footprint.
43 | TP2 | 1 | +3V3 | TestPoint_THTPad_D2.0mm_Drill1.0mm |  |  |  | Optional physical test point; select matching footprint.
44 | TP3 | 1 | PG_BUCK | TestPoint_THTPad_D2.0mm_Drill1.0mm |  |  |  | Optional physical test point; select matching footprint.
45 | TP4 | 1 | GND | TestPoint_THTPad_D2.0mm_Drill1.0mm |  |  |  | Optional physical test point; select matching footprint.
46 | TP5 | 1 | CAN1+ | TestPoint_THTPad_D2.0mm_Drill1.0mm |  |  |  | Optional physical test point; select matching footprint.
47 | TP6 | 1 | CAN1- | TestPoint_THTPad_D2.0mm_Drill1.0mm |  |  |  | Optional physical test point; select matching footprint.
48 | TP7 | 1 | CAN2+ | TestPoint_THTPad_D2.0mm_Drill1.0mm |  |  |  | Optional physical test point; select matching footprint.
49 | TP8 | 1 | CAN2- | TestPoint_THTPad_D2.0mm_Drill1.0mm |  |  |  | Optional physical test point; select matching footprint.
50 | U1 | 1 | LMR33610ADDAR | Texas_HSOP-8-1EP_3.9x4.9mm_P1.27mm_ThermalVias |  | LMR33610ADDAR |  | Match package and ordering suffix. | Part identifier from schematic value; verify exact ordering code.
51 | U2 | 1 | TPS2121RUXR | VQFN-HR-12_L2.5-W2.0-P0.50-BL | TI(德州仪器) | TPS2121RUXR |  | Match package and ordering suffix. | LCSC: C485916
52 | U3 | 1 | ASM330LHHXG1TR | ASM330LHHXG1TR |  | ASM330LHHXG1TR |  | Match package and ordering suffix. | PCB value now matches the schematic (ASM330LHHXG1TR).
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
